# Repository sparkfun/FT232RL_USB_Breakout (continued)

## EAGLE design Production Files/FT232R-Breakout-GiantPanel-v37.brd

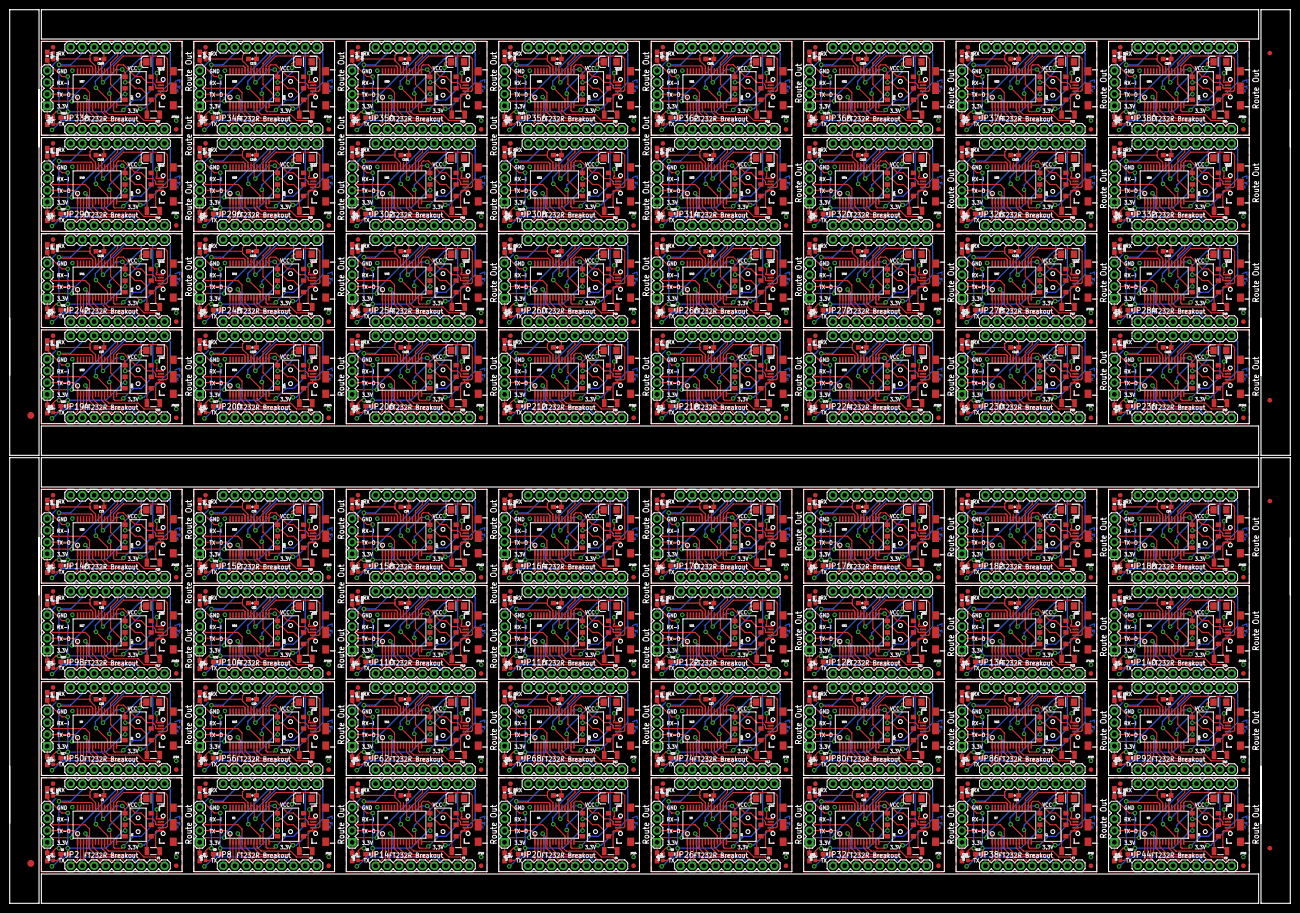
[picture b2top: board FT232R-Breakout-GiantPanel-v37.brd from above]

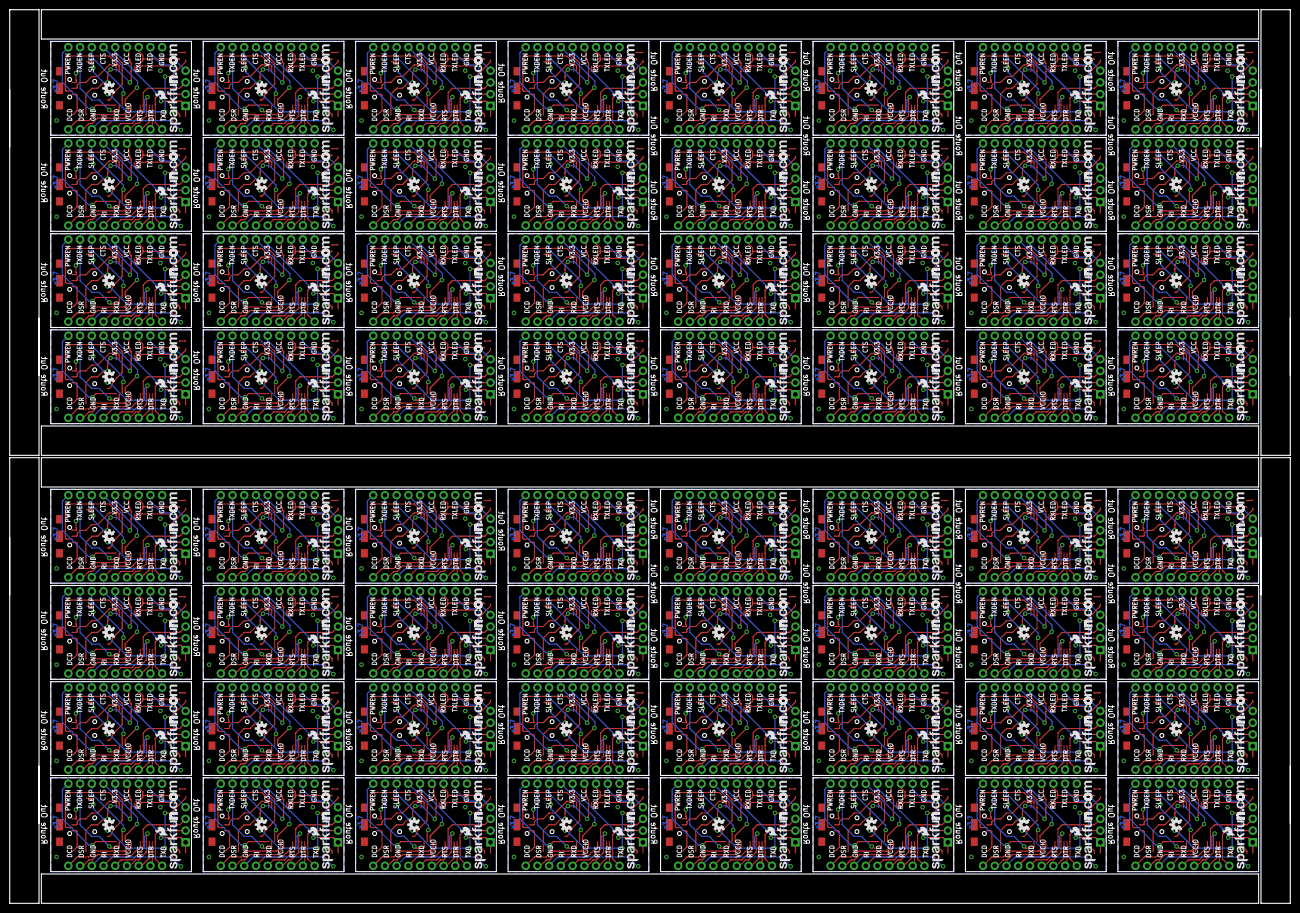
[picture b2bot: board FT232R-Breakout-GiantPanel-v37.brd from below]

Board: 2 copper layers, 277.4 x 193.5 mm, 1158 parts (128 on the bottom side), 1408 nets.

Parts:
C1, C2, C3, C6, C7, C9, C10, C12, C13, C15, C16, C18, C19, C21, C22, C24, C25, C27, C28, C30, C31, C33, C34, C36, C37, C39, C40, C42, C43, C45, C46, C48, C49, C51, C52, C54, C55, C57, C58, C60, C61, C63, C64, C66, C67, C69, C70, C72, C73, C75, C76, C78, C79, C81, C82, C84, C85, C87, C88, C90, C91, C93, C94, C96, C97, C99, C100, C102, C103, C105, C106, C108, C109, C111, C112, C114, C115, C117, C118, C120, C121, C123, C124, C126, C127, C129, C130, C132, C133, C135, C136, C138, C139, C141, C142, C144, C145, C147, C148, C150, C151, C153, C154, C156, C157, C159, C160, C162, C163, C165, C166, C168, C169, C171, C172, C174, C175, C177, C178, C180, C181, C183, C184, C186, C187, C189, C190, C192: 0.1uF; 0603-CAP
C4, C5, C8, C11, C14, C17, C20, C23, C26, C29, C32, C35, C38, C41, C44, C47, C50, C53, C56, C59, C62, C65, C68, C71, C74, C77, C80, C83, C86, C89, C92, C95, C98, C101, C104, C107, C110, C113, C116, C119, C122, C125, C128, C131, C134, C137, C140, C143, C146, C149, C152, C155, C158, C161, C164, C167, C170, C173, C176, C179, C182, C185, C188, C191: 10uF; EIA3216
E$1, E$4: FIDUCIAL-1.5X3
E$2, E$3, E$6, E$8: FIDUCIAL-1X2
F1, F2, F3, F4, F5, F6, F7, F8, F9, F10, F11, F12, F13, F14, F15, F16, F17, F18, F19, F20, F21, F22, F23, F24, F25, F26, F27, F28, F29, F30, F31, F32, F33, F34, F35, F36, F37, F38, F39, F40, F41, F42, F43, F44, F45, F46, F47, F48, F49, F50, F51, F52, F53, F54, F55, F56, F57, F58, F59, F60, F61, F62, F63, F64: 500mA; PTC-1206
JP1, JP2, JP4, JP8, JP13, JP14, JP19, JP20, JP25, JP26, JP31, JP32, JP37, JP38, JP43, JP44, JP49, JP50, JP55, JP56, JP61, JP62, JP67, JP68, JP73, JP74, JP79, JP80, JP85, JP86, JP91, JP92, JP97, JP98, JP103, JP104, JP109, JP110, JP115, JP116, JP121, JP122, JP127, JP128, JP133, JP134, JP139, JP140, JP145, JP146, JP151, JP152, JP157, JP158, JP163, JP164, JP169, JP170, JP175, JP176, JP181, JP182, JP187, JP188, JP193, JP194, JP199, JP200, JP205, JP206, JP211, JP212, JP217, JP218, JP223, JP224, JP229, JP230, JP235, JP236, JP241, JP242, JP247, JP248, JP253, JP254, JP259, JP260, JP265, JP266, JP271, JP272, JP277, JP278, JP283, JP284, JP289, JP290, JP295, JP296, JP301, JP302, JP307, JP308, JP313, JP314, JP319, JP320, JP325, JP326, JP331, JP332, JP337, JP338, JP343, JP344, JP349, JP350, JP355, JP356, JP361, JP362, JP367, JP368, JP373, JP374, JP379, JP380: 1X09
JP3, JP9, JP15, JP21, JP27, JP33, JP39, JP45, JP51, JP57, JP63, JP69, JP75, JP81, JP87, JP93, JP99, JP105, JP111, JP117, JP123, JP129, JP135, JP141, JP147, JP153, JP159, JP165, JP171, JP177, JP183, JP189, JP195, JP201, JP207, JP213, JP219, JP225, JP231, JP237, JP243, JP249, JP255, JP261, JP267, JP273, JP279, JP285, JP291, JP297, JP303, JP309, JP315, JP321, JP327, JP333, JP339, JP345, JP351, JP357, JP363, JP369, JP375, JP381: 1X04
JP5, JP6, JP10, JP11, JP16, JP17, JP22, JP23, JP28, JP29, JP34, JP35, JP40, JP41, JP46, JP47, JP52, JP53, JP58, JP59, JP64, JP65, JP70, JP71, JP76, JP77, JP82, JP83, JP88, JP89, JP94, JP95, JP100, JP101, JP106, JP107, JP112, JP113, JP118, JP119, JP124, JP125, JP130, JP131, JP136, JP137, JP142, JP143, JP148, JP149, JP154, JP155, JP160, JP161, JP166, JP167, JP172, JP173, JP178, JP179, JP184, JP185, JP190, JP191, JP196, JP197, JP202, JP203, JP208, JP209, JP214, JP215, JP220, JP221, JP226, JP227, JP232, JP233, JP238, JP239, JP244, JP245, JP250, JP251, JP256, JP257, JP262, JP263, JP268, JP269, JP274, JP275, JP280, JP281, JP286, JP287, JP292, JP293, JP298, JP299, JP304, JP305, JP310, JP311, JP316, JP317, JP322, JP323, JP328, JP329, JP334, JP335, JP340, JP341, JP346, JP347, JP352, JP353, JP358, JP359, JP364, JP365, JP370, JP371, JP376, JP377, JP382, JP383: FIDUCIAL1X2; FIDUCIAL-1X2
JP7, JP12, JP18, JP24, JP30, JP36, JP42, JP48, JP54, JP60, JP66, JP72, JP78, JP84, JP90, JP96, JP102, JP108, JP114, JP120, JP126, JP132, JP138, JP144, JP150, JP156, JP162, JP168, JP174, JP180, JP186, JP192, JP198, JP204, JP210, JP216, JP222, JP228, JP234, JP240, JP246, JP252, JP258, JP264, JP270, JP276, JP282, JP288, JP294, JP300, JP306, JP312, JP318, JP324, JP330, JP336, JP342, JP348, JP354, JP360, JP366, JP372, JP378, JP384: USB_MICROB_PLUGCONN-11752; USB-B-MICRO-SMD_V03
LED1, LED3, LED5, LED7, LED9, LED11, LED13, LED15, LED17, LED19, LED21, LED23, LED25, LED27, LED29, LED31, LED33, LED35, LED37, LED39, LED41, LED43, LED45, LED47, LED49, LED51, LED53, LED55, LED57, LED59, LED61, LED63, LED65, LED67, LED69, LED71, LED73, LED75, LED77, LED79, LED81, LED83, LED85, LED87, LED89, LED91, LED93, LED95, LED97, LED99, LED101, LED103, LED105, LED107, LED109, LED111, LED113, LED115, LED117, LED119, LED121, LED123, LED125, LED127: Red; LED-0603
LED2, LED4, LED6, LED8, LED10, LED12, LED14, LED16, LED18, LED20, LED22, LED24, LED26, LED28, LED30, LED32, LED34, LED36, LED38, LED40, LED42, LED44, LED46, LED48, LED50, LED52, LED54, LED56, LED58, LED60, LED62, LED64, LED66, LED68, LED70, LED72, LED74, LED76, LED78, LED80, LED82, LED84, LED86, LED88, LED90, LED92, LED94, LED96, LED98, LED100, LED102, LED104, LED106, LED108, LED110, LED112, LED114, LED116, LED118, LED120, LED122, LED124, LED126, LED128: Green; LED-0603
LOGO1, LOGO2, LOGO3, LOGO4, LOGO5, LOGO6, LOGO7, LOGO8, LOGO9, LOGO10, LOGO11, LOGO12, LOGO13, LOGO14, LOGO15, LOGO16, LOGO17, LOGO18, LOGO19, LOGO20, LOGO21, LOGO22, LOGO23, LOGO24, LOGO25, LOGO26, LOGO27, LOGO28, LOGO29, LOGO30, LOGO31, LOGO32, LOGO33, LOGO34, LOGO35, LOGO36, LOGO37, LOGO38, LOGO39, LOGO40, LOGO41, LOGO42, LOGO43, LOGO44, LOGO45, LOGO46, LOGO47, LOGO48, LOGO49, LOGO50, LOGO51, LOGO52, LOGO53, LOGO54, LOGO55, LOGO56, LOGO57, LOGO58, LOGO59, LOGO60, LOGO61, LOGO62, LOGO63, LOGO64: OSHW-LOGOS; OSHW-LOGO-S
R1, R2, R3, R4, R5, R6, R7, R8, R9, R10, R11, R12, R13, R14, R15, R16, R17, R18, R19, R20, R21, R22, R23, R24, R25, R26, R27, R28, R29, R30, R31, R32, R33, R34, R35, R36, R37, R38, R39, R40, R41, R42, R43, R44, R45, R46, R47, R48, R49, R50, R51, R52, R53, R54, R55, R56, R57, R58, R59, R60, R61, R62, R63, R64, R65, R66, R67, R68, R69, R70, R71, R72, R73, R74, R75, R76, R77, R78, R79, R80, R81, R82, R83, R84, R85, R86, R87, R88, R89, R90, R91, R92, R93, R94, R95, R96, R97, R98, R99, R100, R101, R102, R103, R104, R105, R106, R107, R108, R109, R110, R111, R112, R113, R114, R115, R116, R117, R118, R119, R120, R121, R122, R123, R124, R125, R126, R127, R128: 330; 0603-RES
S1, S2, S3, S4, S5, S6, S7, S8, S9, S10, S11, S12, S13, S14, S15, S16, S17, S18, S19, S20, S21, S22, S23, S24, S25, S26, S27, S28, S29, S30, S31, S32, S33, S34, S35, S36, S37, S38, S39, S40, S41, S42, S43, S44, S45, S46, S47, S48, S49, S50, S51, S52, S53, S54, S55, S56, S57, S58, S59, S60, S61, S62, S63, S64: AYZ0202
U1, U2, U3, U4, U5, U6, U7, U8, U9, U10, U11, U12, U13, U14, U15, U16, U17, U18, U19, U20, U21, U22, U23, U24, U25, U26, U27, U28, U29, U30, U31, U32, U33, U34, U35, U36, U37, U38, U39, U40, U41, U42, U43, U44, U45, U46, U47, U48, U49, U50, U51, U52, U53, U54, U55, U56, U57, U58, U59, U60, U61, U62, U63, U64: FT232R; SSOP28DB
U$1, U$2, U$3, U$4, U$5, U$6, U$7, U$8, U$9, U$10, U$11, U$12, U$13, U$14, U$15, U$16, U$17, U$18, U$19, U$20, U$21, U$22, U$23, U$24, U$25, U$26, U$27, U$28, U$29, U$30, U$31, U$32, U$33, U$34, U$35, U$36, U$37, U$38, U$39, U$40, U$41, U$42, U$43, U$44, U$45, U$46, U$47, U$48, U$49, U$50, U$51, U$52, U$53, U$54, U$55, U$56, U$57, U$58, U$59, U$60, U$61, U$62, U$63, U$64: LOGO-SFENEW; SFE-NEW-WEBLOGO

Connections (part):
3.3V: C1.1, JP1.5, JP3.1, S1.1, U1.17
3.3V1: C6.1, JP4.5, JP9.1, S2.1, U2.17
3.3V2: C9.1, JP13.5, JP15.1, S3.1, U3.17
3.3V3: C12.1, JP19.5, JP21.1, S4.1, U4.17
3.3V4: C15.1, JP25.5, JP27.1, S5.1, U5.17
3.3V5: C18.1, JP31.5, JP33.1, S6.1, U6.17
3.3V6: C21.1, JP37.5, JP39.1, S7.1, U7.17
3.3V7: C24.1, JP43.5, JP45.1, S8.1, U8.17
3.3V8: C27.1, JP49.5, JP51.1, S9.1, U9.17
3.3V9: C30.1, JP55.5, JP57.1, S10.1, U10.17
3.3V10: C33.1, JP61.5, JP63.1, S11.1, U11.17
3.3V11: C36.1, JP67.5, JP69.1, S12.1, U12.17
3.3V12: C39.1, JP73.5, JP75.1, S13.1, U13.17
3.3V13: C42.1, JP79.5, JP81.1, S14.1, U14.17
3.3V14: C45.1, JP85.5, JP87.1, S15.1, U15.17
3.3V15: C48.1, JP91.5, JP93.1, S16.1, U16.17
3.3V16: C51.1, JP97.5, JP99.1, S17.1, U17.17
3.3V17: C54.1, JP103.5, JP105.1, S18.1, U18.17
3.3V18: C57.1, JP109.5, JP111.1, S19.1, U19.17
3.3V19: C60.1, JP115.5, JP117.1, S20.1, U20.17
3.3V20: C63.1, JP121.5, JP123.1, S21.1, U21.17
3.3V21: C66.1, JP127.5, JP129.1, S22.1, U22.17
3.3V22: C69.1, JP133.5, JP135.1, S23.1, U23.17
3.3V23: C72.1, JP139.5, JP141.1, S24.1, U24.17
3.3V24: C75.1, JP145.5, JP147.1, S25.1, U25.17
3.3V25: C78.1, JP151.5, JP153.1, S26.1, U26.17
3.3V26: C81.1, JP157.5, JP159.1, S27.1, U27.17
3.3V27: C84.1, JP163.5, JP165.1, S28.1, U28.17
3.3V28: C87.1, JP169.5, JP171.1, S29.1, U29.17
3.3V29: C90.1, JP175.5, JP177.1, S30.1, U30.17
3.3V30: C93.1, JP181.5, JP183.1, S31.1, U31.17
3.3V31: C96.1, JP187.5, JP189.1, S32.1, U32.17
3.3V32: C99.1, JP193.5, JP195.1, S33.1, U33.17
3.3V33: C102.1, JP199.5, JP201.1, S34.1, U34.17
3.3V34: C105.1, JP205.5, JP207.1, S35.1, U35.17
3.3V35: C108.1, JP211.5, JP213.1, S36.1, U36.17
3.3V36: C111.1, JP217.5, JP219.1, S37.1, U37.17
3.3V37: C114.1, JP223.5, JP225.1, S38.1, U38.17
3.3V38: C117.1, JP229.5, JP231.1, S39.1, U39.17
3.3V39: C120.1, JP235.5, JP237.1, S40.1, U40.17
3.3V40: C123.1, JP241.5, JP243.1, S41.1, U41.17
3.3V41: C126.1, JP247.5, JP249.1, S42.1, U42.17
3.3V42: C129.1, JP253.5, JP255.1, S43.1, U43.17
3.3V43: C132.1, JP259.5, JP261.1, S44.1, U44.17
3.3V44: C135.1, JP265.5, JP267.1, S45.1, U45.17
3.3V45: C138.1, JP271.5, JP273.1, S46.1, U46.17
3.3V46: C141.1, JP277.5, JP279.1, S47.1, U47.17
3.3V47: C144.1, JP283.5, JP285.1, S48.1, U48.17
3.3V48: C147.1, JP289.5, JP291.1, S49.1, U49.17
3.3V49: C150.1, JP295.5, JP297.1, S50.1, U50.17
3.3V50: C153.1, JP301.5, JP303.1, S51.1, U51.17
3.3V51: C156.1, JP307.5, JP309.1, S52.1, U52.17
3.3V52: C159.1, JP313.5, JP315.1, S53.1, U53.17
3.3V53: C162.1, JP319.5, JP321.1, S54.1, U54.17
3.3V54: C165.1, JP325.5, JP327.1, S55.1, U55.17
3.3V55: C168.1, JP331.5, JP333.1, S56.1, U56.17
3.3V56: C171.1, JP337.5, JP339.1, S57.1, U57.17
3.3V57: C174.1, JP343.5, JP345.1, S58.1, U58.17
3.3V58: C177.1, JP349.5, JP351.1, S59.1, U59.17
3.3V59: C180.1, JP355.5, JP357.1, S60.1, U60.17
3.3V60: C183.1, JP361.5, JP363.1, S61.1, U61.17
3.3V61: C186.1, JP367.5, JP369.1, S62.1, U62.17
3.3V62: C189.1, JP373.5, JP375.1, S63.1, U63.17
3.3V63: C192.1, JP379.5, JP381.1, S64.1, U64.17
CTS: JP1.6, U1.11
CTS1: JP4.6, U2.11
CTS2: JP13.6, U3.11
CTS3: JP19.6, U4.11
CTS4: JP25.6, U5.11
CTS5: JP31.6, U6.11
CTS6: JP37.6, U7.11
CTS7: JP43.6, U8.11
CTS8: JP49.6, U9.11
CTS9: JP55.6, U10.11
CTS10: JP61.6, U11.11
CTS11: JP67.6, U12.11
CTS12: JP73.6, U13.11
CTS13: JP79.6, U14.11
CTS14: JP85.6, U15.11
CTS15: JP91.6, U16.11
CTS16: JP97.6, U17.11
CTS17: JP103.6, U18.11
CTS18: JP109.6, U19.11
CTS19: JP115.6, U20.11
CTS20: JP121.6, U21.11
CTS21: JP127.6, U22.11
CTS22: JP133.6, U23.11
CTS23: JP139.6, U24.11
CTS24: JP145.6, U25.11
CTS25: JP151.6, U26.11
CTS26: JP157.6, U27.11
CTS27: JP163.6, U28.11
CTS28: JP169.6, U29.11
CTS29: JP175.6, U30.11
CTS30: JP181.6, U31.11
CTS31: JP187.6, U32.11
CTS32: JP193.6, U33.11
CTS33: JP199.6, U34.11
CTS34: JP205.6, U35.11
CTS35: JP211.6, U36.11
CTS36: JP217.6, U37.11
CTS37: JP223.6, U38.11
CTS38: JP229.6, U39.11
CTS39: JP235.6, U40.11
CTS40: JP241.6, U41.11
CTS41: JP247.6, U42.11
CTS42: JP253.6, U43.11
CTS43: JP259.6, U44.11
CTS44: JP265.6, U45.11
CTS45: JP271.6, U46.11
CTS46: JP277.6, U47.11
CTS47: JP283.6, U48.11
CTS48: JP289.6, U49.11
CTS49: JP295.6, U50.11
CTS50: JP301.6, U51.11
CTS51: JP307.6, U52.11
CTS52: JP313.6, U53.11
CTS53: JP319.6, U54.11
CTS54: JP325.6, U55.11
CTS55: JP331.6, U56.11
CTS56: JP337.6, U57.11
CTS57: JP343.6, U58.11
CTS58: JP349.6, U59.11
CTS59: JP355.6, U60.11
CTS60: JP361.6, U61.11
CTS61: JP367.6, U62.11
CTS62: JP373.6, U63.11
CTS63: JP379.6, U64.11
DCD: JP2.9, U1.10
DCD1: JP8.9, U2.10
DCD2: JP14.9, U3.10
DCD3: JP20.9, U4.10
DCD4: JP26.9, U5.10
DCD5: JP32.9, U6.10
DCD6: JP38.9, U7.10
DCD7: JP44.9, U8.10
DCD8: JP50.9, U9.10
DCD9: JP56.9, U10.10
DCD10: JP62.9, U11.10
DCD11: JP68.9, U12.10
DCD12: JP74.9, U13.10
DCD13: JP80.9, U14.10
DCD14: JP86.9, U15.10
DCD15: JP92.9, U16.10
DCD16: JP98.9, U17.10
DCD17: JP104.9, U18.10
DCD18: JP110.9, U19.10
DCD19: JP116.9, U20.10
DCD20: JP122.9, U21.10
DCD21: JP128.9, U22.10
DCD22: JP134.9, U23.10
DCD23: JP140.9, U24.10
DCD24: JP146.9, U25.10
DCD25: JP152.9, U26.10
DCD26: JP158.9, U27.10
DCD27: JP164.9, U28.10
DCD28: JP170.9, U29.10
DCD29: JP176.9, U30.10
DCD30: JP182.9, U31.10
DCD31: JP188.9, U32.10
DCD32: JP194.9, U33.10
DCD33: JP200.9, U34.10
DCD34: JP206.9, U35.10
DCD35: JP212.9, U36.10
DCD36: JP218.9, U37.10
DCD37: JP224.9, U38.10
DCD38: JP230.9, U39.10
DCD39: JP236.9, U40.10
DCD40: JP242.9, U41.10
DCD41: JP248.9, U42.10
DCD42: JP254.9, U43.10
DCD43: JP260.9, U44.10
DCD44: JP266.9, U45.10
DCD45: JP272.9, U46.10
DCD46: JP278.9, U47.10
DCD47: JP284.9, U48.10
DCD48: JP290.9, U49.10
DCD49: JP296.9, U50.10
DCD50: JP302.9, U51.10
DCD51: JP308.9, U52.10
DCD52: JP314.9, U53.10
DCD53: JP320.9, U54.10
DCD54: JP326.9, U55.10
DCD55: JP332.9, U56.10
DCD56: JP338.9, U57.10
DCD57: JP344.9, U58.10
DCD58: JP350.9, U59.10
DCD59: JP356.9, U60.10
DCD60: JP362.9, U61.10
DCD61: JP368.9, U62.10
DCD62: JP374.9, U63.10
DCD63: JP380.9, U64.10
DSR: JP2.8, U1.9
DSR1: JP8.8, U2.9
DSR2: JP14.8, U3.9
DSR3: JP20.8, U4.9
DSR4: JP26.8, U5.9
DSR5: JP32.8, U6.9
DSR6: JP38.8, U7.9
DSR7: JP44.8, U8.9
DSR8: JP50.8, U9.9
DSR9: JP56.8, U10.9
DSR10: JP62.8, U11.9
DSR11: JP68.8, U12.9
DSR12: JP74.8, U13.9
DSR13: JP80.8, U14.9
DSR14: JP86.8, U15.9
DSR15: JP92.8, U16.9
DSR16: JP98.8, U17.9
DSR17: JP104.8, U18.9
DSR18: JP110.8, U19.9
DSR19: JP116.8, U20.9
DSR20: JP122.8, U21.9
DSR21: JP128.8, U22.9
DSR22: JP134.8, U23.9
DSR23: JP140.8, U24.9
DSR24: JP146.8, U25.9
DSR25: JP152.8, U26.9
DSR26: JP158.8, U27.9
DSR27: JP164.8, U28.9
DSR28: JP170.8, U29.9
DSR29: JP176.8, U30.9
DSR30: JP182.8, U31.9
DSR31: JP188.8, U32.9
DSR32: JP194.8, U33.9
DSR33: JP200.8, U34.9
DSR34: JP206.8, U35.9
DSR35: JP212.8, U36.9
DSR36: JP218.8, U37.9
DSR37: JP224.8, U38.9
DSR38: JP230.8, U39.9
DSR39: JP236.8, U40.9
DSR40: JP242.8, U41.9
DSR41: JP248.8, U42.9
DSR42: JP254.8, U43.9
DSR43: JP260.8, U44.9
DSR44: JP266.8, U45.9
DSR45: JP272.8, U46.9
DSR46: JP278.8, U47.9
DSR47: JP284.8, U48.9
DSR48: JP290.8, U49.9
DSR49: JP296.8, U50.9
DSR50: JP302.8, U51.9
DSR51: JP308.8, U52.9
DSR52: JP314.8, U53.9
DSR53: JP320.8, U54.9
DSR54: JP326.8, U55.9
DSR55: JP332.8, U56.9
DSR56: JP338.8, U57.9
DSR57: JP344.8, U58.9
DSR58: JP350.8, U59.9
DSR59: JP356.8, U60.9
DSR60: JP362.8, U61.9
DSR61: JP368.8, U62.9
DSR62: JP374.8, U63.9
DSR63: JP380.8, U64.9
DTR: JP2.2, U1.2
DTR1: JP8.2, U2.2
DTR2: JP14.2, U3.2
DTR3: JP20.2, U4.2
DTR4: JP26.2, U5.2
DTR5: JP32.2, U6.2
DTR6: JP38.2, U7.2
DTR7: JP44.2, U8.2
DTR8: JP50.2, U9.2
DTR9: JP56.2, U10.2
DTR10: JP62.2, U11.2
DTR11: JP68.2, U12.2
DTR12: JP74.2, U13.2
DTR13: JP80.2, U14.2
DTR14: JP86.2, U15.2
DTR15: JP92.2, U16.2
DTR16: JP98.2, U17.2
DTR17: JP104.2, U18.2
DTR18: JP110.2, U19.2
DTR19: JP116.2, U20.2
DTR20: JP122.2, U21.2
DTR21: JP128.2, U22.2
DTR22: JP134.2, U23.2
DTR23: JP140.2, U24.2
DTR24: JP146.2, U25.2
DTR25: JP152.2, U26.2
DTR26: JP158.2, U27.2
DTR27: JP164.2, U28.2
DTR28: JP170.2, U29.2
DTR29: JP176.2, U30.2
DTR30: JP182.2, U31.2
DTR31: JP188.2, U32.2
DTR32: JP194.2, U33.2
DTR33: JP200.2, U34.2
DTR34: JP206.2, U35.2
DTR35: JP212.2, U36.2
DTR36: JP218.2, U37.2
DTR37: JP224.2, U38.2
DTR38: JP230.2, U39.2
DTR39: JP236.2, U40.2
DTR40: JP242.2, U41.2
DTR41: JP248.2, U42.2
DTR42: JP254.2, U43.2
DTR43: JP260.2, U44.2
DTR44: JP266.2, U45.2
DTR45: JP272.2, U46.2
DTR46: JP278.2, U47.2
DTR47: JP284.2, U48.2
DTR48: JP290.2, U49.2
DTR49: JP296.2, U50.2
DTR50: JP302.2, U51.2
DTR51: JP308.2, U52.2
DTR52: JP314.2, U53.2
DTR53: JP320.2, U54.2
DTR54: JP326.2, U55.2
DTR55: JP332.2, U56.2
DTR56: JP338.2, U57.2
DTR57: JP344.2, U58.2
DTR58: JP350.2, U59.2
DTR59: JP356.2, U60.2
DTR60: JP362.2, U61.2
DTR61: JP368.2, U62.2
DTR62: JP374.2, U63.2
DTR63: JP380.2, U64.2
GND: C1.2, C2.2, C5.C, JP1.1, JP2.7, JP3.4, JP7.GND1, U1.7, U1.18, U1.21, U1.25, U1.26
GND1: C3.2, C4.C, C6.2, JP4.1, JP8.7, JP9.4, JP12.GND1, U2.7, U2.18, U2.21, U2.25, U2.26
GND2: C7.2, C8.C, C9.2, JP13.1, JP14.7, JP15.4, JP18.GND1, U3.7, U3.18, U3.21, U3.25, U3.26
GND3: C10.2, C11.C, C12.2, JP19.1, JP20.7, JP21.4, JP24.GND1, U4.7, U4.18, U4.21, U4.25, U4.26
GND4: C13.2, C14.C, C15.2, JP25.1, JP26.7, JP27.4, JP30.GND1, U5.7, U5.18, U5.21, U5.25, U5.26
GND5: C16.2, C17.C, C18.2, JP31.1, JP32.7, JP33.4, JP36.GND1, U6.7, U6.18, U6.21, U6.25, U6.26
GND6: C19.2, C20.C, C21.2, JP37.1, JP38.7, JP39.4, JP42.GND1, U7.7, U7.18, U7.21, U7.25, U7.26
GND7: C22.2, C23.C, C24.2, JP43.1, JP44.7, JP45.4, JP48.GND1, U8.7, U8.18, U8.21, U8.25, U8.26
GND8: C25.2, C26.C, C27.2, JP49.1, JP50.7, JP51.4, JP54.GND1, U9.7, U9.18, U9.21, U9.25, U9.26
GND9: C28.2, C29.C, C30.2, JP55.1, JP56.7, JP57.4, JP60.GND1, U10.7, U10.18, U10.21, U10.25, U10.26
GND10: C31.2, C32.C, C33.2, JP61.1, JP62.7, JP63.4, JP66.GND1, U11.7, U11.18, U11.21, U11.25, U11.26
GND11: C34.2, C35.C, C36.2, JP67.1, JP68.7, JP69.4, JP72.GND1, U12.7, U12.18, U12.21, U12.25, U12.26
GND12: C37.2, C38.C, C39.2, JP73.1, JP74.7, JP75.4, JP78.GND1, U13.7, U13.18, U13.21, U13.25, U13.26
GND13: C40.2, C41.C, C42.2, JP79.1, JP80.7, JP81.4, JP84.GND1, U14.7, U14.18, U14.21, U14.25, U14.26
GND14: C43.2, C44.C, C45.2, JP85.1, JP86.7, JP87.4, JP90.GND1, U15.7, U15.18, U15.21, U15.25, U15.26
GND15: C46.2, C47.C, C48.2, JP91.1, JP92.7, JP93.4, JP96.GND1, U16.7, U16.18, U16.21, U16.25, U16.26
GND16: C49.2, C50.C, C51.2, JP97.1, JP98.7, JP99.4, JP102.GND1, U17.7, U17.18, U17.21, U17.25, U17.26
GND17: C52.2, C53.C, C54.2, JP103.1, JP104.7, JP105.4, JP108.GND1, U18.7, U18.18, U18.21, U18.25, U18.26
GND18: C55.2, C56.C, C57.2, JP109.1, JP110.7, JP111.4, JP114.GND1, U19.7, U19.18, U19.21, U19.25, U19.26
GND19: C58.2, C59.C, C60.2, JP115.1, JP116.7, JP117.4, JP120.GND1, U20.7, U20.18, U20.21, U20.25, U20.26
GND20: C61.2, C62.C, C63.2, JP121.1, JP122.7, JP123.4, JP126.GND1, U21.7, U21.18, U21.21, U21.25, U21.26
GND21: C64.2, C65.C, C66.2, JP127.1, JP128.7, JP129.4, JP132.GND1, U22.7, U22.18, U22.21, U22.25, U22.26
GND22: C67.2, C68.C, C69.2, JP133.1, JP134.7, JP135.4, JP138.GND1, U23.7, U23.18, U23.21, U23.25, U23.26
GND23: C70.2, C71.C, C72.2, JP139.1, JP140.7, JP141.4, JP144.GND1, U24.7, U24.18, U24.21, U24.25, U24.26
GND24: C73.2, C74.C, C75.2, JP145.1, JP146.7, JP147.4, JP150.GND1, U25.7, U25.18, U25.21, U25.25, U25.26
GND25: C76.2, C77.C, C78.2, JP151.1, JP152.7, JP153.4, JP156.GND1, U26.7, U26.18, U26.21, U26.25, U26.26
GND26: C79.2, C80.C, C81.2, JP157.1, JP158.7, JP159.4, JP162.GND1, U27.7, U27.18, U27.21, U27.25, U27.26
GND27: C82.2, C83.C, C84.2, JP163.1, JP164.7, JP165.4, JP168.GND1, U28.7, U28.18, U28.21, U28.25, U28.26
GND28: C85.2, C86.C, C87.2, JP169.1, JP170.7, JP171.4, JP174.GND1, U29.7, U29.18, U29.21, U29.25, U29.26
GND29: C88.2, C89.C, C90.2, JP175.1, JP176.7, JP177.4, JP180.GND1, U30.7, U30.18, U30.21, U30.25, U30.26
GND30: C91.2, C92.C, C93.2, JP181.1, JP182.7, JP183.4, JP186.GND1, U31.7, U31.18, U31.21, U31.25, U31.26
GND31: C94.2, C95.C, C96.2, JP187.1, JP188.7, JP189.4, JP192.GND1, U32.7, U32.18, U32.21, U32.25, U32.26
GND32: C97.2, C98.C, C99.2, JP193.1, JP194.7, JP195.4, JP198.GND1, U33.7, U33.18, U33.21, U33.25, U33.26
GND33: C100.2, C101.C, C102.2, JP199.1, JP200.7, JP201.4, JP204.GND1, U34.7, U34.18, U34.21, U34.25, U34.26
GND34: C103.2, C104.C, C105.2, JP205.1, JP206.7, JP207.4, JP210.GND1, U35.7, U35.18, U35.21, U35.25, U35.26
GND35: C106.2, C107.C, C108.2, JP211.1, JP212.7, JP213.4, JP216.GND1, U36.7, U36.18, U36.21, U36.25, U36.26
GND36: C109.2, C110.C, C111.2, JP217.1, JP218.7, JP219.4, JP222.GND1, U37.7, U37.18, U37.21, U37.25, U37.26
GND37: C112.2, C113.C, C114.2, JP223.1, JP224.7, JP225.4, JP228.GND1, U38.7, U38.18, U38.21, U38.25, U38.26
GND38: C115.2, C116.C, C117.2, JP229.1, JP230.7, JP231.4, JP234.GND1, U39.7, U39.18, U39.21, U39.25, U39.26
GND39: C118.2, C119.C, C120.2, JP235.1, JP236.7, JP237.4, JP240.GND1, U40.7, U40.18, U40.21, U40.25, U40.26
GND40: C121.2, C122.C, C123.2, JP241.1, JP242.7, JP243.4, JP246.GND1, U41.7, U41.18, U41.21, U41.25, U41.26
GND41: C124.2, C125.C, C126.2, JP247.1, JP248.7, JP249.4, JP252.GND1, U42.7, U42.18, U42.21, U42.25, U42.26
GND42: C127.2, C128.C, C129.2, JP253.1, JP254.7, JP255.4, JP258.GND1, U43.7, U43.18, U43.21, U43.25, U43.26
GND43: C130.2, C131.C, C132.2, JP259.1, JP260.7, JP261.4, JP264.GND1, U44.7, U44.18, U44.21, U44.25, U44.26
GND44: C133.2, C134.C, C135.2, JP265.1, JP266.7, JP267.4, JP270.GND1, U45.7, U45.18, U45.21, U45.25, U45.26
GND45: C136.2, C137.C, C138.2, JP271.1, JP272.7, JP273.4, JP276.GND1, U46.7, U46.18, U46.21, U46.25, U46.26
GND46: C139.2, C140.C, C141.2, JP277.1, JP278.7, JP279.4, JP282.GND1, U47.7, U47.18, U47.21, U47.25, U47.26
GND47: C142.2, C143.C, C144.2, JP283.1, JP284.7, JP285.4, JP288.GND1, U48.7, U48.18, U48.21, U48.25, U48.26
GND48: C145.2, C146.C, C147.2, JP289.1, JP290.7, JP291.4, JP294.GND1, U49.7, U49.18, U49.21, U49.25, U49.26
GND49: C148.2, C149.C, C150.2, JP295.1, JP296.7, JP297.4, JP300.GND1, U50.7, U50.18, U50.21, U50.25, U50.26
GND50: C151.2, C152.C, C153.2, JP301.1, JP302.7, JP303.4, JP306.GND1, U51.7, U51.18, U51.21, U51.25, U51.26
GND51: C154.2, C155.C, C156.2, JP307.1, JP308.7, JP309.4, JP312.GND1, U52.7, U52.18, U52.21, U52.25, U52.26
GND52: C157.2, C158.C, C159.2, JP313.1, JP314.7, JP315.4, JP318.GND1, U53.7, U53.18, U53.21, U53.25, U53.26
GND53: C160.2, C161.C, C162.2, JP319.1, JP320.7, JP321.4, JP324.GND1, U54.7, U54.18, U54.21, U54.25, U54.26
GND54: C163.2, C164.C, C165.2, JP325.1, JP326.7, JP327.4, JP330.GND1, U55.7, U55.18, U55.21, U55.25, U55.26
GND55: C166.2, C167.C, C168.2, JP331.1, JP332.7, JP333.4, JP336.GND1, U56.7, U56.18, U56.21, U56.25, U56.26
GND56: C169.2, C170.C, C171.2, JP337.1, JP338.7, JP339.4, JP342.GND1, U57.7, U57.18, U57.21, U57.25, U57.26
GND57: C172.2, C173.C, C174.2, JP343.1, JP344.7, JP345.4, JP348.GND1, U58.7, U58.18, U58.21, U58.25, U58.26
GND58: C175.2, C176.C, C177.2, JP349.1, JP350.7, JP351.4, JP354.GND1, U59.7, U59.18, U59.21, U59.25, U59.26
GND59: C178.2, C179.C, C180.2, JP355.1, JP356.7, JP357.4, JP360.GND1, U60.7, U60.18, U60.21, U60.25, U60.26
GND60: C181.2, C182.C, C183.2, JP361.1, JP362.7, JP363.4, JP366.GND1, U61.7, U61.18, U61.21, U61.25, U61.26
GND61: C184.2, C185.C, C186.2, JP367.1, JP368.7, JP369.4, JP372.GND1, U62.7, U62.18, U62.21, U62.25, U62.26
GND62: C187.2, C188.C, C189.2, JP373.1, JP374.7, JP375.4, JP378.GND1, U63.7, U63.18, U63.21, U63.25, U63.26
GND63: C190.2, C191.C, C192.2, JP379.1, JP380.7, JP381.4, JP384.GND1, U64.7, U64.18, U64.21, U64.25, U64.26
unnamed: LED1.A, R1.1
unnamed: LED2.A, R2.1
unnamed: F1.1, JP7.VBUS1
unnamed: LED3.A, R3.1
unnamed: LED4.A, R4.1
unnamed: F2.1, JP12.VBUS1
unnamed: LED5.A, R5.1
unnamed: LED6.A, R6.1
unnamed: F3.1, JP18.VBUS1
unnamed: LED7.A, R7.1
unnamed: LED8.A, R8.1
unnamed: F4.1, JP24.VBUS1
unnamed: LED9.A, R9.1
unnamed: LED10.A, R10.1
unnamed: F5.1, JP30.VBUS1
unnamed: LED11.A, R11.1
unnamed: LED12.A, R12.1
unnamed: F6.1, JP36.VBUS1
unnamed: LED13.A, R13.1
unnamed: LED14.A, R14.1
unnamed: F7.1, JP42.VBUS1
unnamed: LED15.A, R15.1
unnamed: LED16.A, R16.1
unnamed: F8.1, JP48.VBUS1
unnamed: LED17.A, R17.1
unnamed: LED18.A, R18.1
unnamed: F9.1, JP54.VBUS1
unnamed: LED19.A, R19.1
unnamed: LED20.A, R20.1
unnamed: F10.1, JP60.VBUS1
unnamed: LED21.A, R21.1
unnamed: LED22.A, R22.1
unnamed: F11.1, JP66.VBUS1
unnamed: LED23.A, R23.1
unnamed: LED24.A, R24.1
unnamed: F12.1, JP72.VBUS1
unnamed: LED25.A, R25.1
unnamed: LED26.A, R26.1
unnamed: F13.1, JP78.VBUS1
unnamed: LED27.A, R27.1
unnamed: LED28.A, R28.1
unnamed: F14.1, JP84.VBUS1
unnamed: LED29.A, R29.1
unnamed: LED30.A, R30.1
unnamed: F15.1, JP90.VBUS1
unnamed: LED31.A, R31.1
unnamed: LED32.A, R32.1
unnamed: F16.1, JP96.VBUS1
unnamed: LED33.A, R33.1
unnamed: LED34.A, R34.1
unnamed: F17.1, JP102.VBUS1
unnamed: LED35.A, R35.1
unnamed: LED36.A, R36.1
unnamed: F18.1, JP108.VBUS1
unnamed: LED37.A, R37.1
unnamed: LED38.A, R38.1
unnamed: F19.1, JP114.VBUS1
unnamed: LED39.A, R39.1
unnamed: LED40.A, R40.1
unnamed: F20.1, JP120.VBUS1
unnamed: LED41.A, R41.1
unnamed: LED42.A, R42.1
unnamed: F21.1, JP126.VBUS1
unnamed: LED43.A, R43.1
unnamed: LED44.A, R44.1
unnamed: F22.1, JP132.VBUS1
unnamed: LED45.A, R45.1
unnamed: LED46.A, R46.1
unnamed: F23.1, JP138.VBUS1
unnamed: LED47.A, R47.1
unnamed: LED48.A, R48.1
unnamed: F24.1, JP144.VBUS1
unnamed: LED49.A, R49.1
unnamed: LED50.A, R50.1
unnamed: F25.1, JP150.VBUS1
unnamed: LED51.A, R51.1
unnamed: LED52.A, R52.1
unnamed: F26.1, JP156.VBUS1
unnamed: LED53.A, R53.1
unnamed: LED54.A, R54.1
unnamed: F27.1, JP162.VBUS1
unnamed: LED55.A, R55.1
unnamed: LED56.A, R56.1
unnamed: F28.1, JP168.VBUS1
unnamed: LED57.A, R57.1
unnamed: LED58.A, R58.1
unnamed: F29.1, JP174.VBUS1
unnamed: LED59.A, R59.1
unnamed: LED60.A, R60.1
unnamed: F30.1, JP180.VBUS1
unnamed: LED61.A, R61.1
unnamed: LED62.A, R62.1
unnamed: F31.1, JP186.VBUS1
unnamed: LED63.A, R63.1
unnamed: LED64.A, R64.1
unnamed: F32.1, JP192.VBUS1
unnamed: LED65.A, R65.1
unnamed: LED66.A, R66.1
unnamed: F33.1, JP198.VBUS1
unnamed: LED67.A, R67.1
unnamed: LED68.A, R68.1
unnamed: F34.1, JP204.VBUS1
unnamed: LED69.A, R69.1
unnamed: LED70.A, R70.1
unnamed: F35.1, JP210.VBUS1
unnamed: LED71.A, R71.1
unnamed: LED72.A, R72.1
unnamed: F36.1, JP216.VBUS1
unnamed: LED73.A, R73.1
unnamed: LED74.A, R74.1
unnamed: F37.1, JP222.VBUS1
unnamed: LED75.A, R75.1
unnamed: LED76.A, R76.1
unnamed: F38.1, JP228.VBUS1
unnamed: LED77.A, R77.1
unnamed: LED78.A, R78.1
unnamed: F39.1, JP234.VBUS1
unnamed: LED79.A, R79.1
unnamed: LED80.A, R80.1
unnamed: F40.1, JP240.VBUS1
unnamed: LED81.A, R81.1
unnamed: LED82.A, R82.1
unnamed: F41.1, JP246.VBUS1
unnamed: LED83.A, R83.1
unnamed: LED84.A, R84.1
unnamed: F42.1, JP252.VBUS1
unnamed: LED85.A, R85.1
unnamed: LED86.A, R86.1
unnamed: F43.1, JP258.VBUS1
unnamed: LED87.A, R87.1
unnamed: LED88.A, R88.1
unnamed: F44.1, JP264.VBUS1
unnamed: LED89.A, R89.1
unnamed: LED90.A, R90.1
unnamed: F45.1, JP270.VBUS1
unnamed: LED91.A, R91.1
unnamed: LED92.A, R92.1
unnamed: F46.1, JP276.VBUS1
unnamed: LED93.A, R93.1
unnamed: LED94.A, R94.1
unnamed: F47.1, JP282.VBUS1
unnamed: LED95.A, R95.1
unnamed: LED96.A, R96.1
unnamed: F48.1, JP288.VBUS1
unnamed: LED97.A, R97.1
unnamed: LED98.A, R98.1
unnamed: F49.1, JP294.VBUS1
unnamed: LED99.A, R99.1
unnamed: LED100.A, R100.1
unnamed: F50.1, JP300.VBUS1
unnamed: LED101.A, R101.1
unnamed: LED102.A, R102.1
unnamed: F51.1, JP306.VBUS1
unnamed: LED103.A, R103.1
unnamed: LED104.A, R104.1
unnamed: F52.1, JP312.VBUS1
unnamed: LED105.A, R105.1
unnamed: LED106.A, R106.1
unnamed: F53.1, JP318.VBUS1
unnamed: LED107.A, R107.1
unnamed: LED108.A, R108.1
unnamed: F54.1, JP324.VBUS1
unnamed: LED109.A, R109.1
unnamed: LED110.A, R110.1
unnamed: F55.1, JP330.VBUS1
unnamed: LED111.A, R111.1
unnamed: LED112.A, R112.1
unnamed: F56.1, JP336.VBUS1
unnamed: LED113.A, R113.1
unnamed: LED114.A, R114.1
unnamed: F57.1, JP342.VBUS1
unnamed: LED115.A, R115.1
unnamed: LED116.A, R116.1
unnamed: F58.1, JP348.VBUS1
unnamed: LED117.A, R117.1
unnamed: LED118.A, R118.1
unnamed: F59.1, JP354.VBUS1
unnamed: LED119.A, R119.1
unnamed: LED120.A, R120.1
unnamed: F60.1, JP360.VBUS1
unnamed: LED121.A, R121.1
unnamed: LED122.A, R122.1
unnamed: F61.1, JP366.VBUS1
unnamed: LED123.A, R123.1
unnamed: LED124.A, R124.1
unnamed: F62.1, JP372.VBUS1
unnamed: LED125.A, R125.1
unnamed: LED126.A, R126.1
unnamed: F63.1, JP378.VBUS1
unnamed: LED127.A, R127.1
unnamed: LED128.A, R128.1
unnamed: F64.1, JP384.VBUS1
PWREN: JP1.9, U1.14
PWREN1: JP4.9, U2.14
PWREN2: JP13.9, U3.14
PWREN3: JP19.9, U4.14
PWREN4: JP25.9, U5.14
PWREN5: JP31.9, U6.14
PWREN6: JP37.9, U7.14
PWREN7: JP43.9, U8.14
PWREN8: JP49.9, U9.14
PWREN9: JP55.9, U10.14
PWREN10: JP61.9, U11.14
PWREN11: JP67.9, U12.14
PWREN12: JP73.9, U13.14
PWREN13: JP79.9, U14.14
PWREN14: JP85.9, U15.14
PWREN15: JP91.9, U16.14
PWREN16: JP97.9, U17.14
PWREN17: JP103.9, U18.14
PWREN18: JP109.9, U19.14
PWREN19: JP115.9, U20.14
PWREN20: JP121.9, U21.14
PWREN21: JP127.9, U22.14
PWREN22: JP133.9, U23.14
PWREN23: JP139.9, U24.14
PWREN24: JP145.9, U25.14
PWREN25: JP151.9, U26.14
PWREN26: JP157.9, U27.14
PWREN27: JP163.9, U28.14
PWREN28: JP169.9, U29.14
PWREN29: JP175.9, U30.14
PWREN30: JP181.9, U31.14
PWREN31: JP187.9, U32.14
PWREN32: JP193.9, U33.14
PWREN33: JP199.9, U34.14
PWREN34: JP205.9, U35.14
PWREN35: JP211.9, U36.14
PWREN36: JP217.9, U37.14
PWREN37: JP223.9, U38.14
PWREN38: JP229.9, U39.14
PWREN39: JP235.9, U40.14
PWREN40: JP241.9, U41.14
PWREN41: JP247.9, U42.14
PWREN42: JP253.9, U43.14
PWREN43: JP259.9, U44.14
PWREN44: JP265.9, U45.14
PWREN45: JP271.9, U46.14
PWREN46: JP277.9, U47.14
PWREN47: JP283.9, U48.14
PWREN48: JP289.9, U49.14
PWREN49: JP295.9, U50.14
PWREN50: JP301.9, U51.14
PWREN51: JP307.9, U52.14
PWREN52: JP313.9, U53.14
PWREN53: JP319.9, U54.14
PWREN54: JP325.9, U55.14
PWREN55: JP331.9, U56.14
PWREN56: JP337.9, U57.14
PWREN57: JP343.9, U58.14
PWREN58: JP349.9, U59.14
PWREN59: JP355.9, U60.14
PWREN60: JP361.9, U61.14
PWREN61: JP367.9, U62.14
PWREN62: JP373.9, U63.14
PWREN63: JP379.9, U64.14
RI: JP2.6, U1.6
RI1: JP8.6, U2.6
RI2: JP14.6, U3.6
RI3: JP20.6, U4.6
RI4: JP26.6, U5.6
RI5: JP32.6, U6.6
RI6: JP38.6, U7.6
RI7: JP44.6, U8.6
RI8: JP50.6, U9.6
RI9: JP56.6, U10.6
RI10: JP62.6, U11.6
RI11: JP68.6, U12.6
RI12: JP74.6, U13.6
RI13: JP80.6, U14.6
RI14: JP86.6, U15.6
RI15: JP92.6, U16.6
RI16: JP98.6, U17.6
RI17: JP104.6, U18.6
RI18: JP110.6, U19.6
RI19: JP116.6, U20.6
RI20: JP122.6, U21.6
RI21: JP128.6, U22.6
RI22: JP134.6, U23.6
RI23: JP140.6, U24.6
RI24: JP146.6, U25.6
RI25: JP152.6, U26.6
RI26: JP158.6, U27.6
RI27: JP164.6, U28.6
RI28: JP170.6, U29.6
RI29: JP176.6, U30.6
RI30: JP182.6, U31.6
RI31: JP188.6, U32.6
RI32: JP194.6, U33.6
RI33: JP200.6, U34.6
RI34: JP206.6, U35.6
RI35: JP212.6, U36.6
RI36: JP218.6, U37.6
RI37: JP224.6, U38.6
RI38: JP230.6, U39.6
RI39: JP236.6, U40.6
RI40: JP242.6, U41.6
RI41: JP248.6, U42.6
RI42: JP254.6, U43.6
RI43: JP260.6, U44.6
RI44: JP266.6, U45.6
RI45: JP272.6, U46.6
RI46: JP278.6, U47.6
RI47: JP284.6, U48.6
RI48: JP290.6, U49.6
RI49: JP296.6, U50.6
RI50: JP302.6, U51.6
RI51: JP308.6, U52.6
RI52: JP314.6, U53.6
RI53: JP320.6, U54.6
RI54: JP326.6, U55.6
RI55: JP332.6, U56.6
RI56: JP338.6, U57.6
RI57: JP344.6, U58.6
RI58: JP350.6, U59.6
RI59: JP356.6, U60.6
RI60: JP362.6, U61.6
RI61: JP368.6, U62.6
RI62: JP374.6, U63.6
RI63: JP380.6, U64.6
RTS: JP2.3, U1.3
RTS1: JP8.3, U2.3
RTS2: JP14.3, U3.3
RTS3: JP20.3, U4.3
RTS4: JP26.3, U5.3
RTS5: JP32.3, U6.3
RTS6: JP38.3, U7.3
RTS7: JP44.3, U8.3
RTS8: JP50.3, U9.3
RTS9: JP56.3, U10.3
RTS10: JP62.3, U11.3
RTS11: JP68.3, U12.3
RTS12: JP74.3, U13.3
RTS13: JP80.3, U14.3
RTS14: JP86.3, U15.3
RTS15: JP92.3, U16.3
RTS16: JP98.3, U17.3
RTS17: JP104.3, U18.3
RTS18: JP110.3, U19.3
RTS19: JP116.3, U20.3
RTS20: JP122.3, U21.3
RTS21: JP128.3, U22.3
RTS22: JP134.3, U23.3
RTS23: JP140.3, U24.3
RTS24: JP146.3, U25.3
RTS25: JP152.3, U26.3
RTS26: JP158.3, U27.3
RTS27: JP164.3, U28.3
RTS28: JP170.3, U29.3
RTS29: JP176.3, U30.3
RTS30: JP182.3, U31.3
RTS31: JP188.3, U32.3
RTS32: JP194.3, U33.3
RTS33: JP200.3, U34.3
RTS34: JP206.3, U35.3
RTS35: JP212.3, U36.3
RTS36: JP218.3, U37.3
RTS37: JP224.3, U38.3
RTS38: JP230.3, U39.3
RTS39: JP236.3, U40.3
RTS40: JP242.3, U41.3
RTS41: JP248.3, U42.3
RTS42: JP254.3, U43.3
RTS43: JP260.3, U44.3
RTS44: JP266.3, U45.3
RTS45: JP272.3, U46.3
RTS46: JP278.3, U47.3
RTS47: JP284.3, U48.3
RTS48: JP290.3, U49.3
RTS49: JP296.3, U50.3
RTS50: JP302.3, U51.3
RTS51: JP308.3, U52.3
RTS52: JP314.3, U53.3
RTS53: JP320.3, U54.3
RTS54: JP326.3, U55.3
RTS55: JP332.3, U56.3
RTS56: JP338.3, U57.3
RTS57: JP344.3, U58.3
RTS58: JP350.3, U59.3
RTS59: JP356.3, U60.3
RTS60: JP362.3, U61.3
RTS61: JP368.3, U62.3
RTS62: JP374.3, U63.3
RTS63: JP380.3, U64.3
RXD: JP2.5, JP3.3, U1.5
RXD1: JP8.5, JP9.3, U2.5
RXD2: JP14.5, JP15.3, U3.5
RXD3: JP20.5, JP21.3, U4.5
RXD4: JP26.5, JP27.3, U5.5
RXD5: JP32.5, JP33.3, U6.5
RXD6: JP38.5, JP39.3, U7.5
RXD7: JP44.5, JP45.3, U8.5
RXD8: JP50.5, JP51.3, U9.5
RXD9: JP56.5, JP57.3, U10.5
RXD10: JP62.5, JP63.3, U11.5
RXD11: JP68.5, JP69.3, U12.5
RXD12: JP74.5, JP75.3, U13.5
RXD13: JP80.5, JP81.3, U14.5
RXD14: JP86.5, JP87.3, U15.5
RXD15: JP92.5, JP93.3, U16.5
RXD16: JP98.5, JP99.3, U17.5
RXD17: JP104.5, JP105.3, U18.5
RXD18: JP110.5, JP111.3, U19.5
RXD19: JP116.5, JP117.3, U20.5
RXD20: JP122.5, JP123.3, U21.5
RXD21: JP128.5, JP129.3, U22.5
RXD22: JP134.5, JP135.3, U23.5
RXD23: JP140.5, JP141.3, U24.5
RXD24: JP146.5, JP147.3, U25.5
RXD25: JP152.5, JP153.3, U26.5
RXD26: JP158.5, JP159.3, U27.5
RXD27: JP164.5, JP165.3, U28.5
RXD28: JP170.5, JP171.3, U29.5
RXD29: JP176.5, JP177.3, U30.5
RXD30: JP182.5, JP183.3, U31.5
RXD31: JP188.5, JP189.3, U32.5
RXD32: JP194.5, JP195.3, U33.5
RXD33: JP200.5, JP201.3, U34.5
RXD34: JP206.5, JP207.3, U35.5
RXD35: JP212.5, JP213.3, U36.5
RXD36: JP218.5, JP219.3, U37.5
RXD37: JP224.5, JP225.3, U38.5
RXD38: JP230.5, JP231.3, U39.5
RXD39: JP236.5, JP237.3, U40.5
RXD40: JP242.5, JP243.3, U41.5
RXD41: JP248.5, JP249.3, U42.5
RXD42: JP254.5, JP255.3, U43.5
RXD43: JP260.5, JP261.3, U44.5
RXD44: JP266.5, JP267.3, U45.5
RXD45: JP272.5, JP273.3, U46.5
RXD46: JP278.5, JP279.3, U47.5
RXD47: JP284.5, JP285.3, U48.5
RXD48: JP290.5, JP291.3, U49.5
RXD49: JP296.5, JP297.3, U50.5
RXD50: JP302.5, JP303.3, U51.5
RXD51: JP308.5, JP309.3, U52.5
RXD52: JP314.5, JP315.3, U53.5
RXD53: JP320.5, JP321.3, U54.5
RXD54: JP326.5, JP327.3, U55.5
RXD55: JP332.5, JP333.3, U56.5
RXD56: JP338.5, JP339.3, U57.5
RXD57: JP344.5, JP345.3, U58.5
RXD58: JP350.5, JP351.3, U59.5
RXD59: JP356.5, JP357.3, U60.5
RXD60: JP362.5, JP363.3, U61.5
RXD61: JP368.5, JP369.3, U62.5
RXD62: JP374.5, JP375.3, U63.5
RXD63: JP380.5, JP381.3, U64.5
RXLED: JP1.3, LED2.C, U1.22
RXLED1: JP4.3, LED4.C, U2.22
RXLED2: JP13.3, LED6.C, U3.22
RXLED3: JP19.3, LED8.C, U4.22
RXLED4: JP25.3, LED10.C, U5.22
RXLED5: JP31.3, LED12.C, U6.22
RXLED6: JP37.3, LED14.C, U7.22
RXLED7: JP43.3, LED16.C, U8.22
RXLED8: JP49.3, LED18.C, U9.22
RXLED9: JP55.3, LED20.C, U10.22
RXLED10: JP61.3, LED22.C, U11.22
RXLED11: JP67.3, LED24.C, U12.22
RXLED12: JP73.3, LED26.C, U13.22
RXLED13: JP79.3, LED28.C, U14.22
RXLED14: JP85.3, LED30.C, U15.22
RXLED15: JP91.3, LED32.C, U16.22
RXLED16: JP97.3, LED34.C, U17.22
RXLED17: JP103.3, LED36.C, U18.22
RXLED18: JP109.3, LED38.C, U19.22
RXLED19: JP115.3, LED40.C, U20.22
RXLED20: JP121.3, LED42.C, U21.22
RXLED21: JP127.3, LED44.C, U22.22
RXLED22: JP133.3, LED46.C, U23.22
RXLED23: JP139.3, LED48.C, U24.22
RXLED24: JP145.3, LED50.C, U25.22
RXLED25: JP151.3, LED52.C, U26.22
RXLED26: JP157.3, LED54.C, U27.22
RXLED27: JP163.3, LED56.C, U28.22
RXLED28: JP169.3, LED58.C, U29.22
RXLED29: JP175.3, LED60.C, U30.22
RXLED30: JP181.3, LED62.C, U31.22
RXLED31: JP187.3, LED64.C, U32.22
RXLED32: JP193.3, LED66.C, U33.22
RXLED33: JP199.3, LED68.C, U34.22
RXLED34: JP205.3, LED70.C, U35.22
RXLED35: JP211.3, LED72.C, U36.22
RXLED36: JP217.3, LED74.C, U37.22
RXLED37: JP223.3, LED76.C, U38.22
RXLED38: JP229.3, LED78.C, U39.22
RXLED39: JP235.3, LED80.C, U40.22
RXLED40: JP241.3, LED82.C, U41.22
RXLED41: JP247.3, LED84.C, U42.22
RXLED42: JP253.3, LED86.C, U43.22
RXLED43: JP259.3, LED88.C, U44.22
RXLED44: JP265.3, LED90.C, U45.22
RXLED45: JP271.3, LED92.C, U46.22
RXLED46: JP277.3, LED94.C, U47.22
RXLED47: JP283.3, LED96.C, U48.22
RXLED48: JP289.3, LED98.C, U49.22
RXLED49: JP295.3, LED100.C, U50.22
RXLED50: JP301.3, LED102.C, U51.22
RXLED51: JP307.3, LED104.C, U52.22
RXLED52: JP313.3, LED106.C, U53.22
RXLED53: JP319.3, LED108.C, U54.22
RXLED54: JP325.3, LED110.C, U55.22
RXLED55: JP331.3, LED112.C, U56.22
RXLED56: JP337.3, LED114.C, U57.22
RXLED57: JP343.3, LED116.C, U58.22
RXLED58: JP349.3, LED118.C, U59.22
RXLED59: JP355.3, LED120.C, U60.22
RXLED60: JP361.3, LED122.C, U61.22
RXLED61: JP367.3, LED124.C, U62.22
RXLED62: JP373.3, LED126.C, U63.22
RXLED63: JP379.3, LED128.C, U64.22
SLEEP: JP1.7, U1.12
SLEEP1: JP4.7, U2.12
SLEEP2: JP13.7, U3.12
SLEEP3: JP19.7, U4.12
SLEEP4: JP25.7, U5.12
SLEEP5: JP31.7, U6.12
SLEEP6: JP37.7, U7.12
SLEEP7: JP43.7, U8.12
SLEEP8: JP49.7, U9.12
SLEEP9: JP55.7, U10.12
SLEEP10: JP61.7, U11.12
SLEEP11: JP67.7, U12.12
SLEEP12: JP73.7, U13.12
SLEEP13: JP79.7, U14.12
SLEEP14: JP85.7, U15.12
SLEEP15: JP91.7, U16.12
SLEEP16: JP97.7, U17.12
SLEEP17: JP103.7, U18.12
SLEEP18: JP109.7, U19.12
SLEEP19: JP115.7, U20.12
SLEEP20: JP121.7, U21.12
SLEEP21: JP127.7, U22.12
SLEEP22: JP133.7, U23.12
SLEEP23: JP139.7, U24.12
SLEEP24: JP145.7, U25.12
SLEEP25: JP151.7, U26.12
SLEEP26: JP157.7, U27.12
SLEEP27: JP163.7, U28.12
SLEEP28: JP169.7, U29.12
SLEEP29: JP175.7, U30.12
SLEEP30: JP181.7, U31.12
SLEEP31: JP187.7, U32.12
SLEEP32: JP193.7, U33.12
SLEEP33: JP199.7, U34.12
SLEEP34: JP205.7, U35.12
SLEEP35: JP211.7, U36.12
SLEEP36: JP217.7, U37.12
SLEEP37: JP223.7, U38.12
SLEEP38: JP229.7, U39.12
SLEEP39: JP235.7, U40.12
SLEEP40: JP241.7, U41.12
SLEEP41: JP247.7, U42.12
SLEEP42: JP253.7, U43.12
SLEEP43: JP259.7, U44.12
SLEEP44: JP265.7, U45.12
SLEEP45: JP271.7, U46.12
SLEEP46: JP277.7, U47.12
SLEEP47: JP283.7, U48.12
SLEEP48: JP289.7, U49.12
SLEEP49: JP295.7, U50.12
SLEEP50: JP301.7, U51.12
SLEEP51: JP307.7, U52.12
SLEEP52: JP313.7, U53.12
SLEEP53: JP319.7, U54.12
SLEEP54: JP325.7, U55.12
SLEEP55: JP331.7, U56.12
SLEEP56: JP337.7, U57.12
SLEEP57: JP343.7, U58.12
SLEEP58: JP349.7, U59.12
SLEEP59: JP355.7, U60.12
SLEEP60: JP361.7, U61.12
SLEEP61: JP367.7, U62.12
SLEEP62: JP373.7, U63.12
SLEEP63: JP379.7, U64.12
TXD: JP2.1, JP3.2, U1.1
TXD1: JP8.1, JP9.2, U2.1
TXD2: JP14.1, JP15.2, U3.1
TXD3: JP20.1, JP21.2, U4.1
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
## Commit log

2013-12-11 Adding hardware files and updating README
2014-01-25 Adding v3.7 files
2014-01-29 Adding SMD switch for 3.3V/ 5V selection
2014-03-06 Removing paste spot left over from last version
2014-03-07 Centering USB connector
2014-03-11 Updating rev with recommendations from review
2014-04-01 created giant panel v37
2014-12-08 Updating README with new product links
2025-06-27 Update README.md~
    Updating links.
